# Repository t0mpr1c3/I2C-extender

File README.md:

I2C-extender
============

Reversible P82B715 breakout board with daisy-chainable I2C header.

See datasheet for calculation of pullup resistor values. Optional clamp diodes and zeners for EMI/ESD protection. 

Released under the [Creative Commons License Attribution-ShareAlike 3.0](http://creativecommons.org/licenses/by-sa/3.0/)

Revision history
----------------

_IX01_

First version

_IX02_

Corrected typo on silk screen

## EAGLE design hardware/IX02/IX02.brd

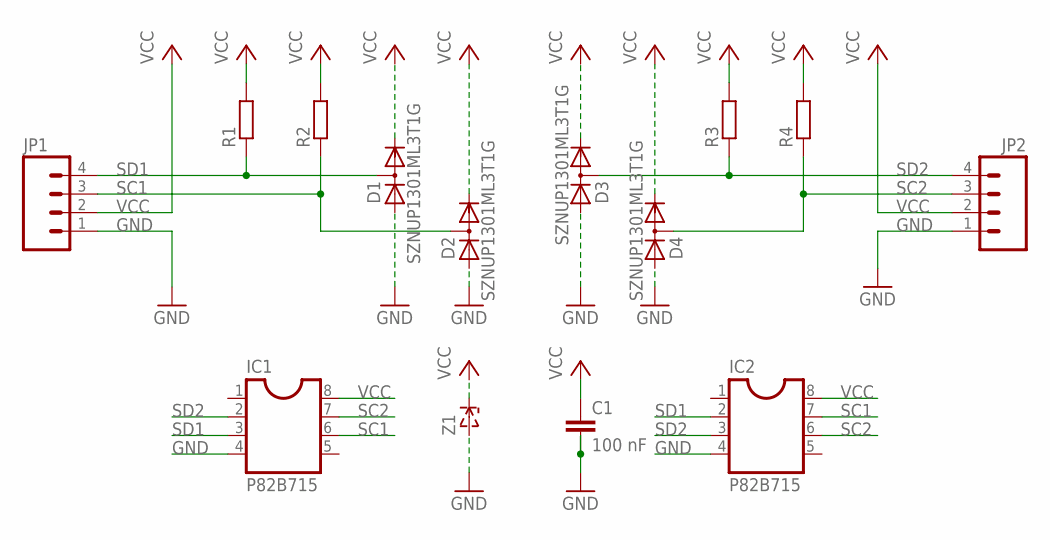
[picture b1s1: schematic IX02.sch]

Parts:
C1: 100 nF; C0805
D1, D2, D3, D4: SZNUP1301ML3T1G; SOT23
IC1, IC2: P82B715; SO-8
JP1, JP2: M04PTH; 1X04
R1, R2, R3, R4: R-EU_R0805; R0805
Z1: ZENERSOD-323F; SOD-323F

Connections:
GND: C1.2, D1.1 (A), D2.1 (A), D3.1 (A), D4.1 (A), IC1.4, IC2.4, JP1.1, JP2.1, Z1.A
SC1: D2.3 (AC), IC1.6, IC2.7, JP1.3, R2.1
SC2: D4.3 (AC), IC1.7, IC2.6, JP2.3, R4.1
SD1: D1.3 (AC), IC1.3, IC2.2, JP1.4, R1.1
SD2: D3.3 (AC), IC1.2, IC2.3, JP2.4, R3.1
VCC: C1.1, D1.2 (C), D2.2 (C), D3.2 (C), D4.2 (C), IC1.8, IC2.8, JP1.2, JP2.2, R1.2, R2.2, R3.2, R4.2, Z1.C

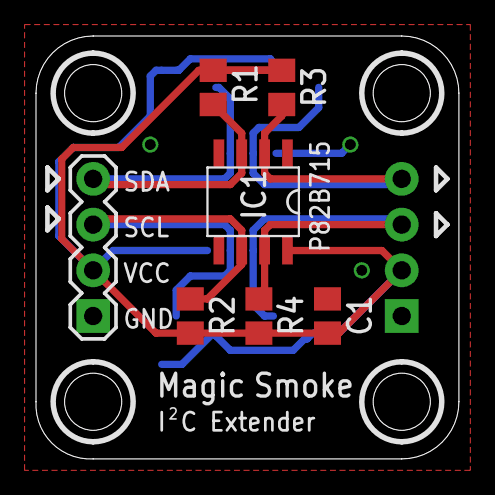
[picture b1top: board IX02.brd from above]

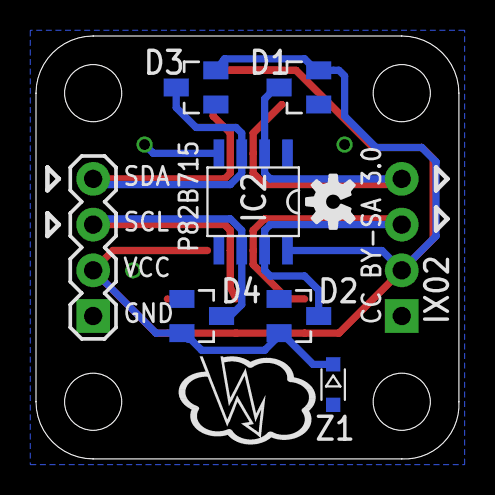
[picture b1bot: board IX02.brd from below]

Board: 4 copper layers, 23.5 x 23.5 mm, 15 parts (8 on the bottom side), 6 nets.

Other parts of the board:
U$3: OSHW-LOGO-S

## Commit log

2013-12-01 tweak gerbers
2013-12-03 IX01 for Seeedstudio
2013-12-03 IX01 Elecrow order
2013-12-24 corrected typo on silk screen

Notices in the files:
hardware/IX02/IX02.brd:
CC BY-SA 3.0
parts and their libraries:
SparkFun: Licensing: CC v3.0 Share-Alike You are welcome to use this library for commercial purposes.
